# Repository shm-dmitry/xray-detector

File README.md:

V3 version in progress.
V2 version details:

xray-detector, based on SBT-11A sensor, combined with powerbank futures.

At this moment project finished. Everething works, but with several UI-bugs :)

I will fix them in future, but basically project finished.

Features:
- xray-detector on SBT-11A sensor (senses beta & gamma radiation)
- history in sievert, monthly dose, graph with last severall minutes
- beta-radiation rameasurement feature
- flashlight :-)
- powerbank
- long battery life (about half-year) without recharging
- Simple upgrade firmware - Flushing USB port can be accessed with-out unboxing

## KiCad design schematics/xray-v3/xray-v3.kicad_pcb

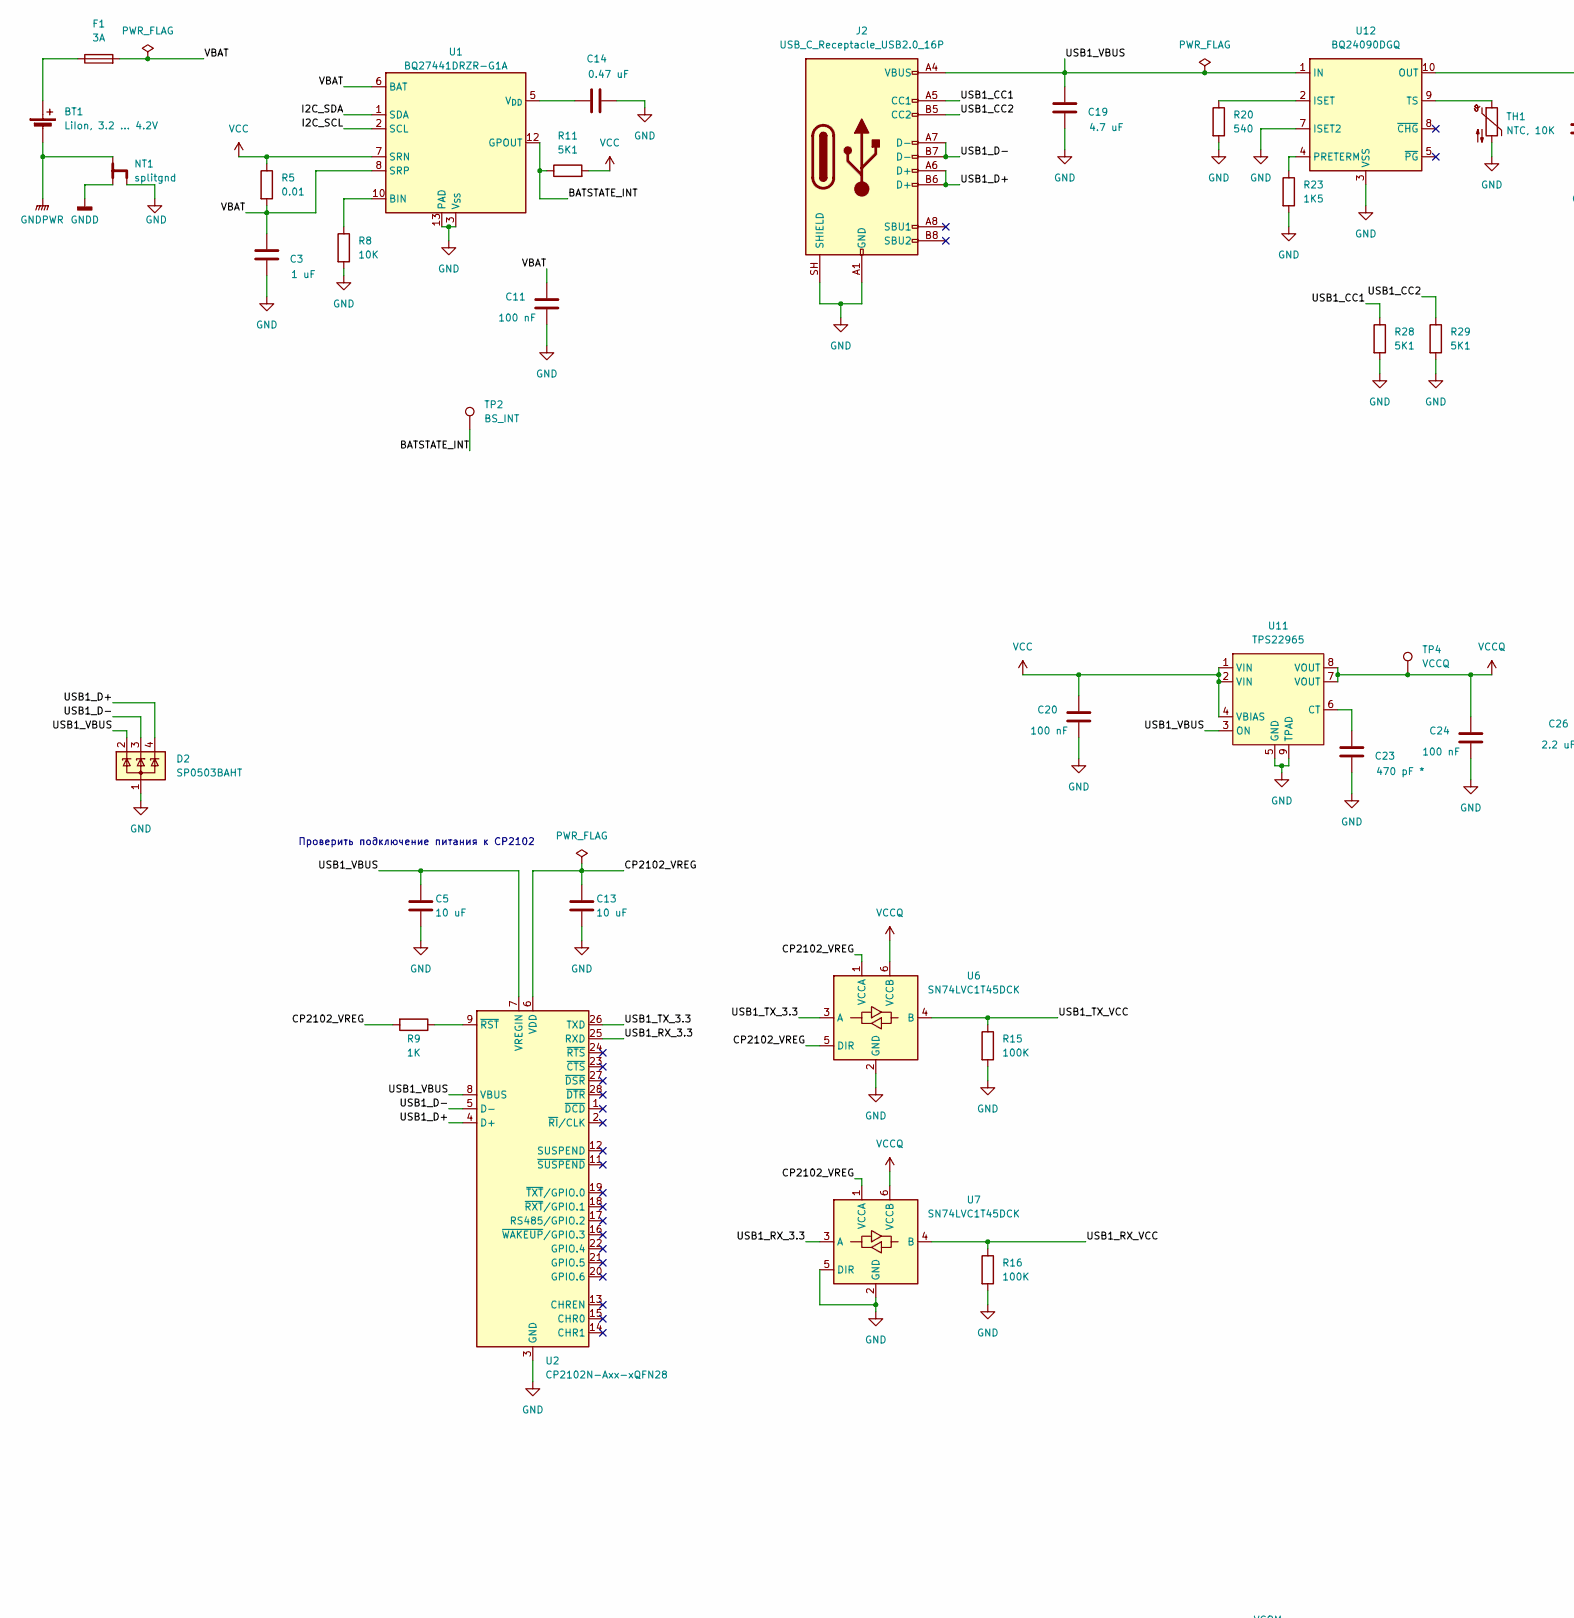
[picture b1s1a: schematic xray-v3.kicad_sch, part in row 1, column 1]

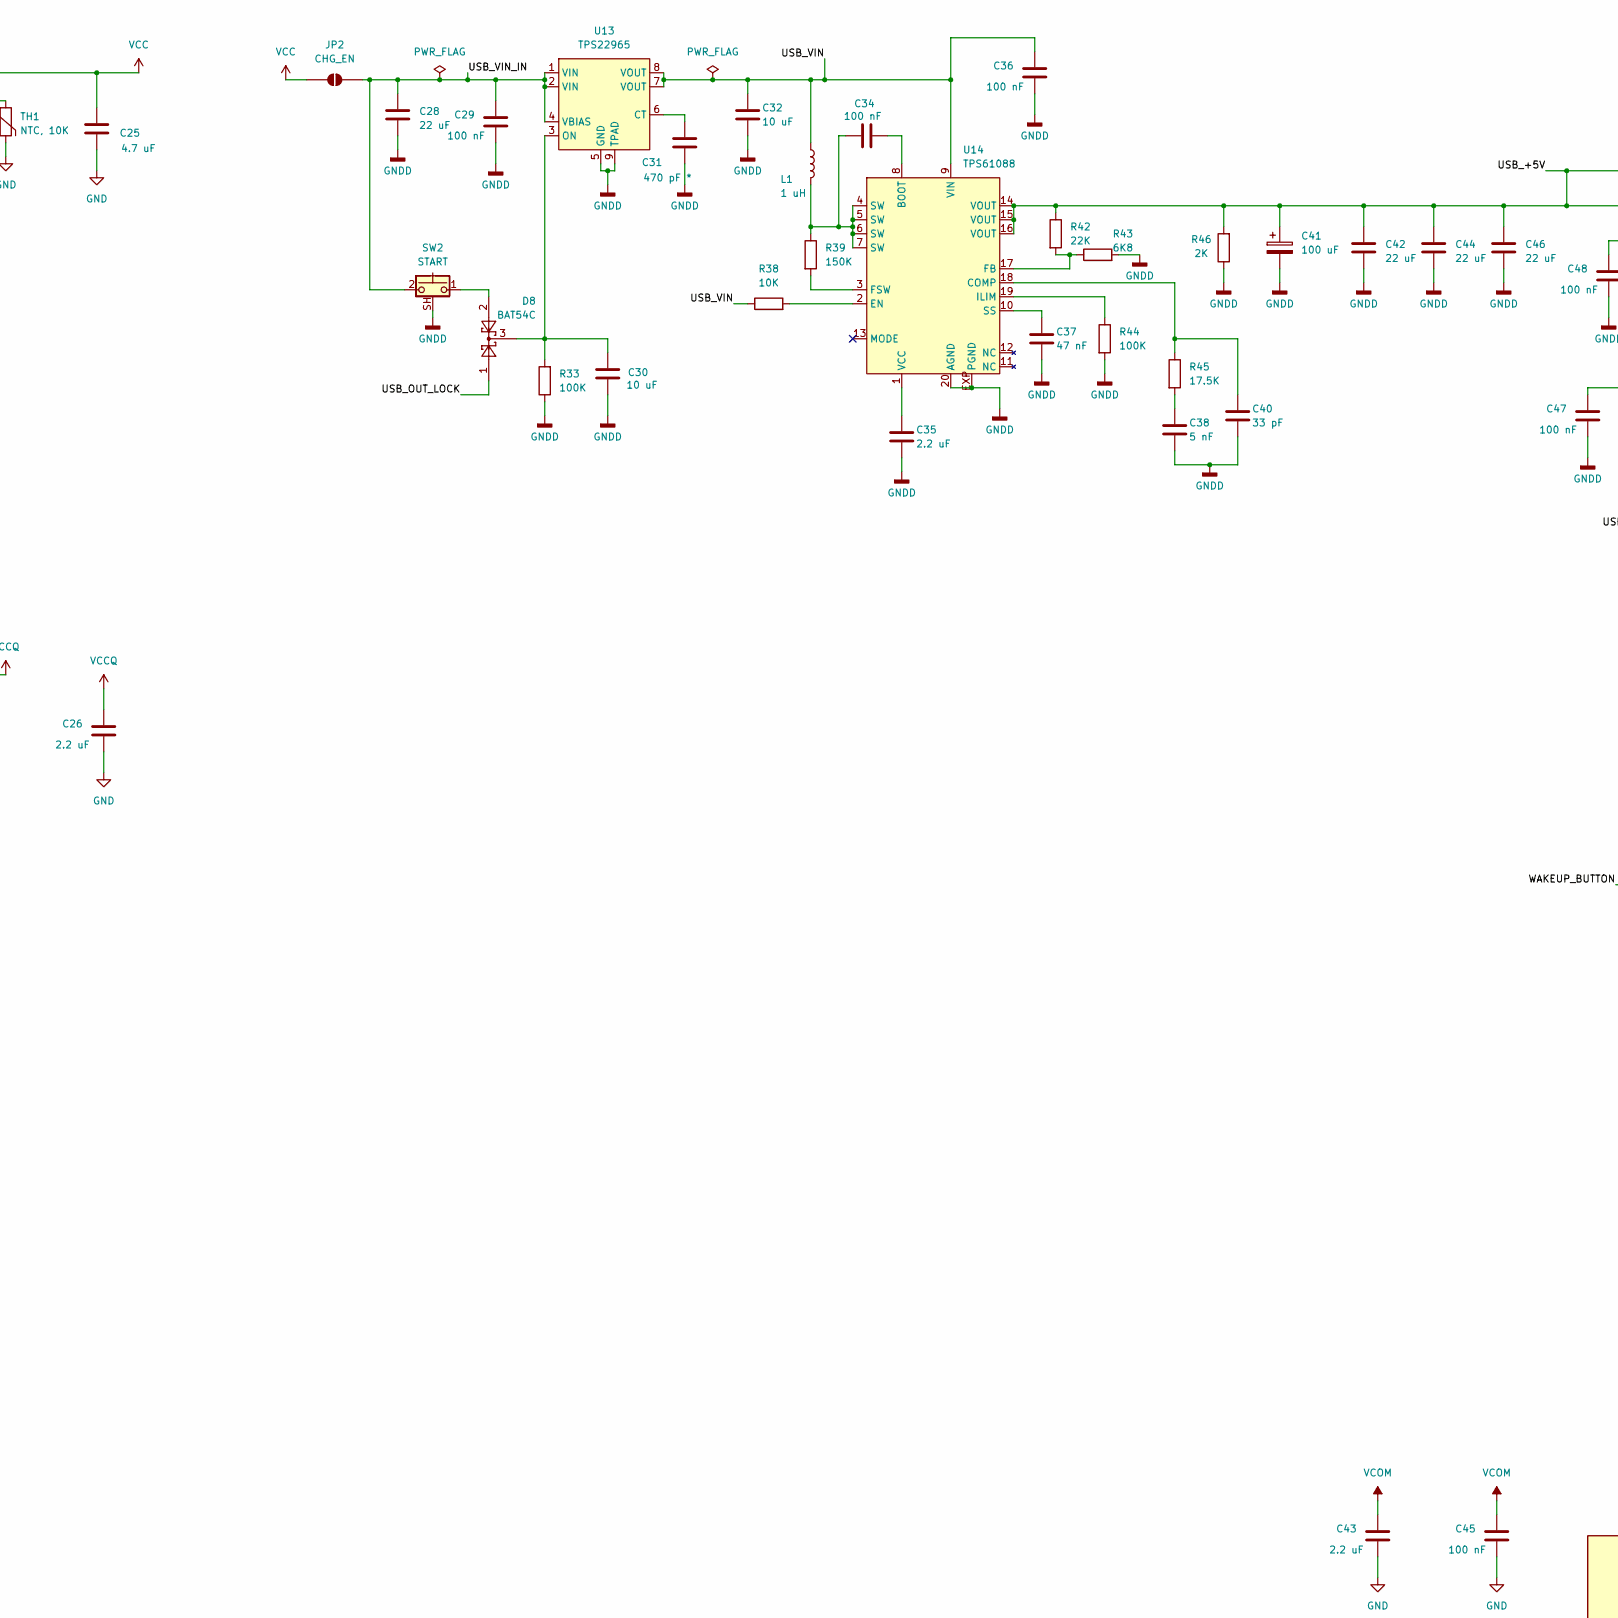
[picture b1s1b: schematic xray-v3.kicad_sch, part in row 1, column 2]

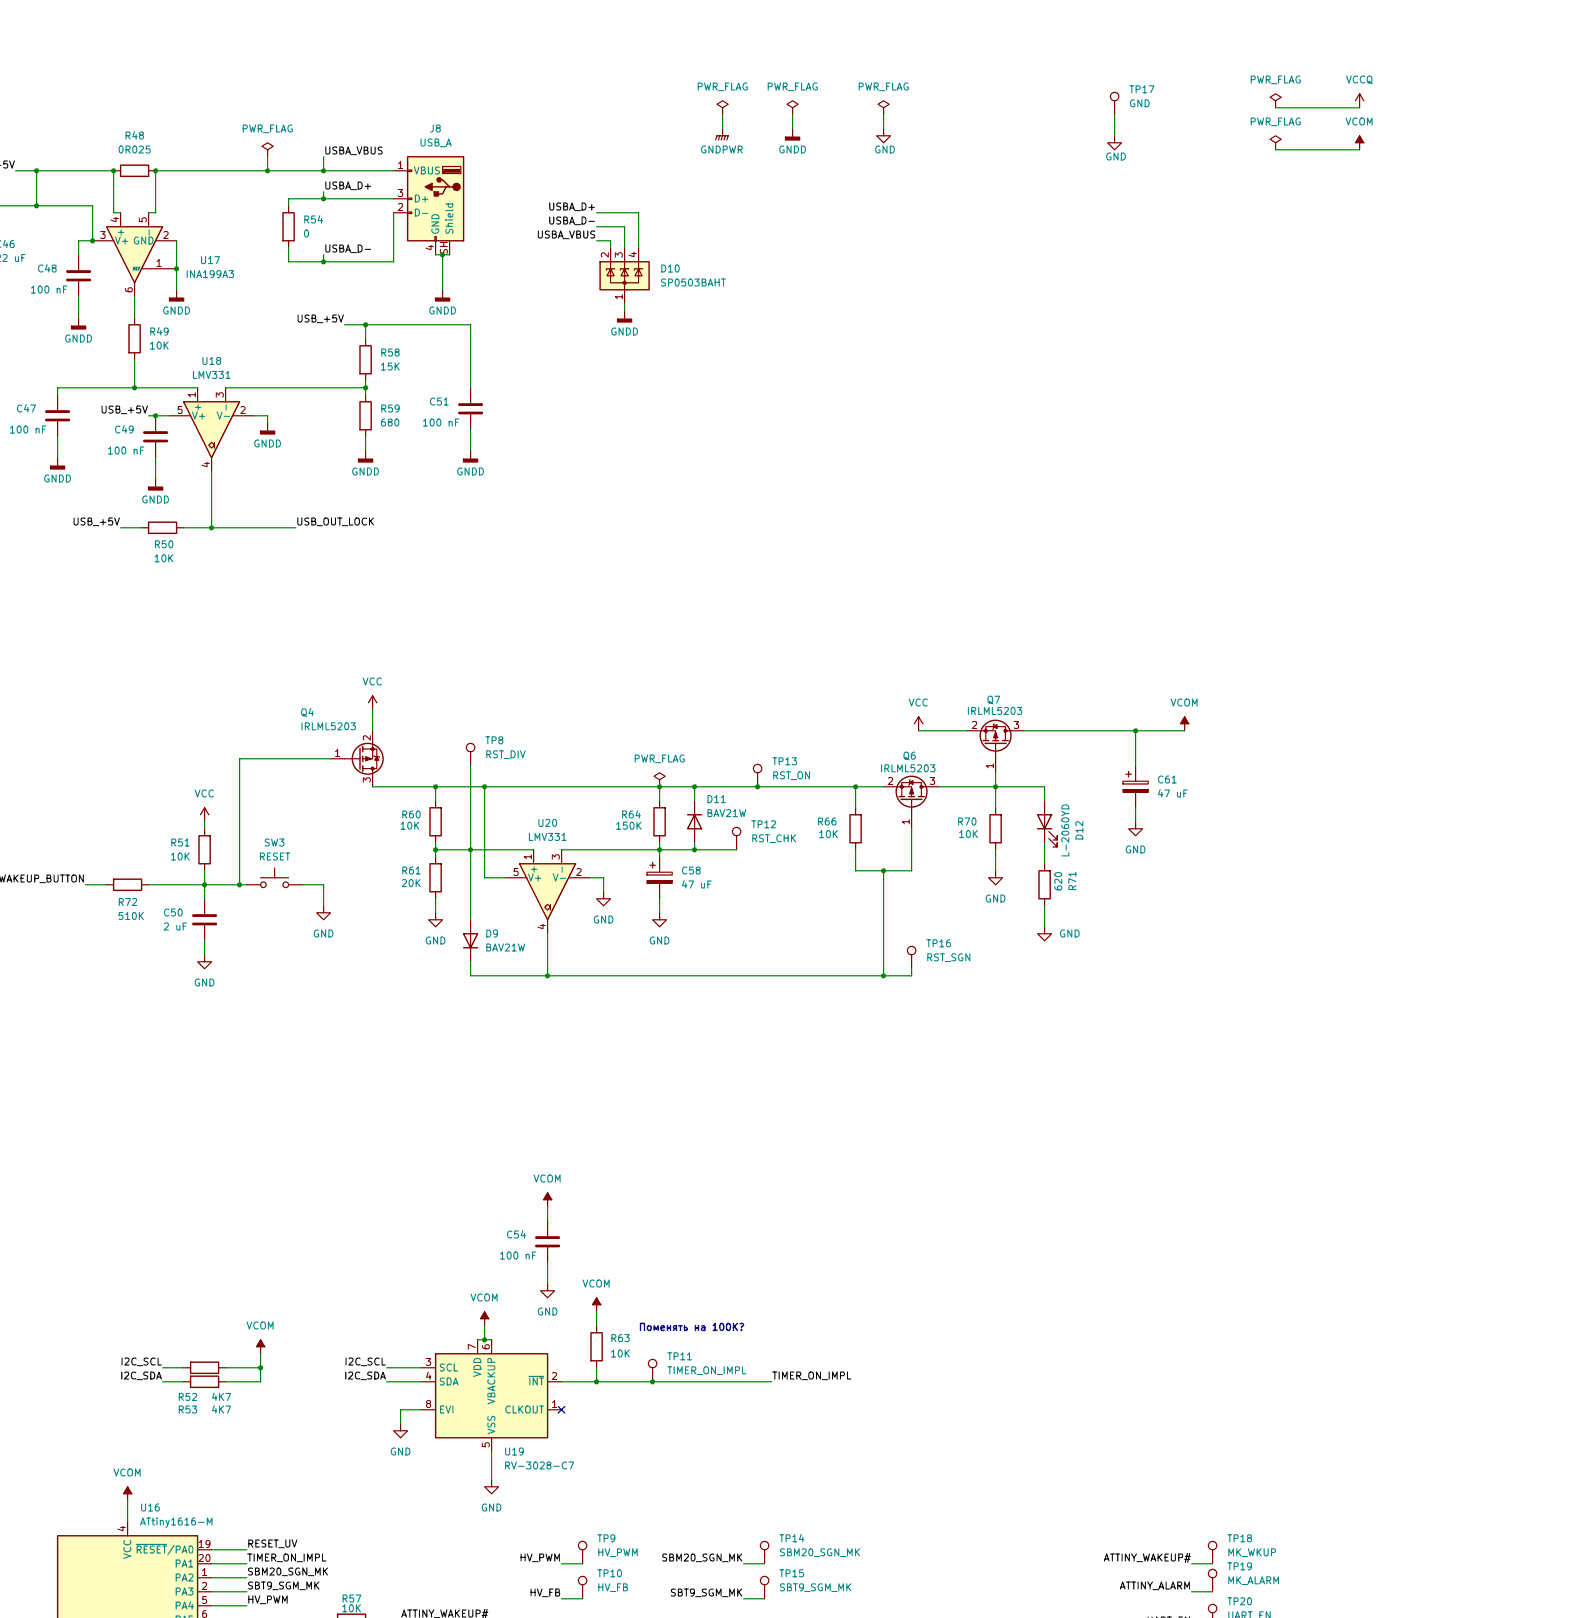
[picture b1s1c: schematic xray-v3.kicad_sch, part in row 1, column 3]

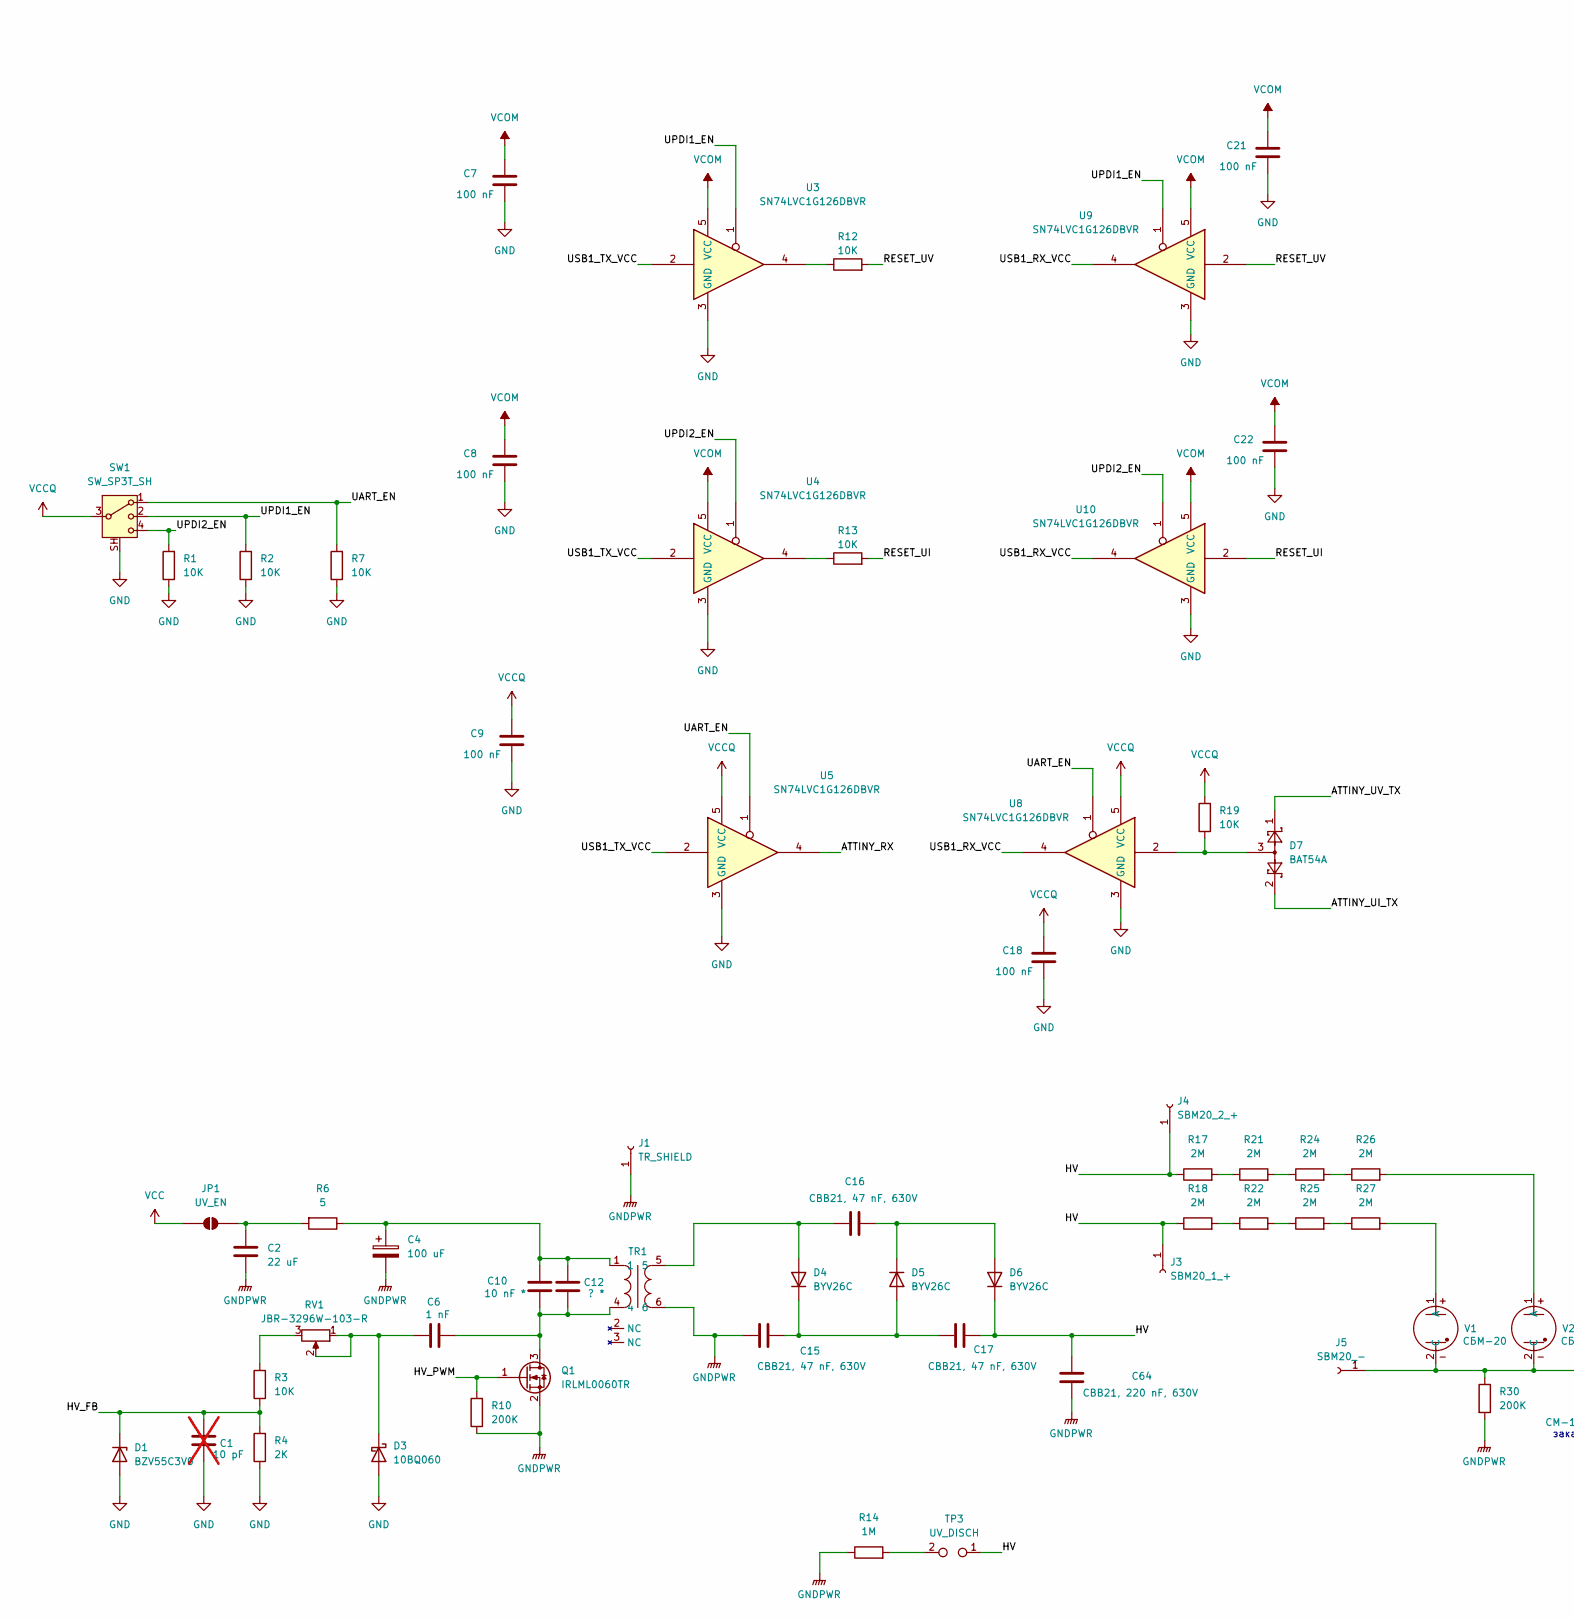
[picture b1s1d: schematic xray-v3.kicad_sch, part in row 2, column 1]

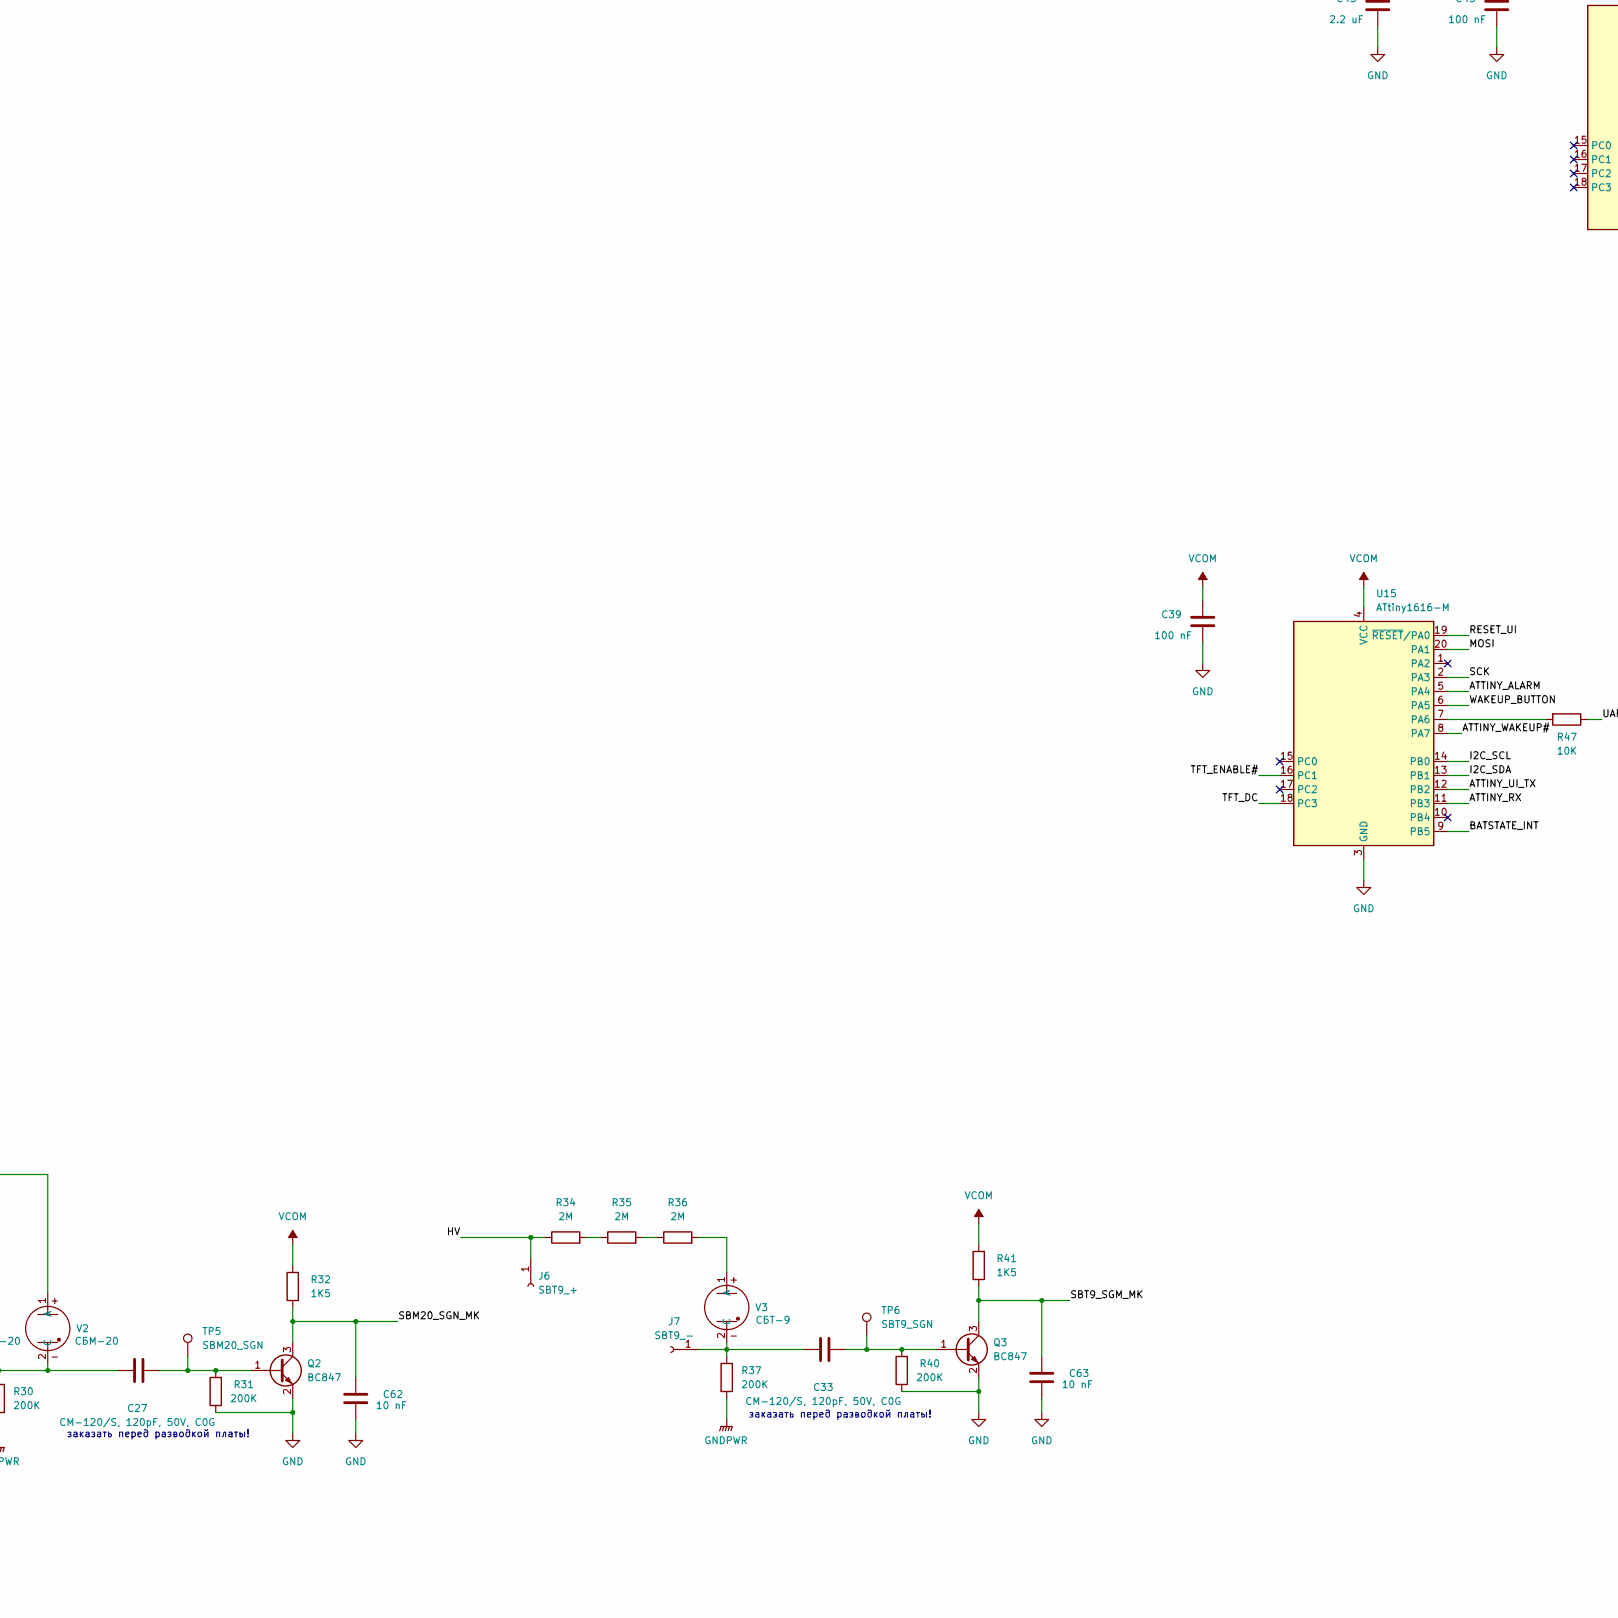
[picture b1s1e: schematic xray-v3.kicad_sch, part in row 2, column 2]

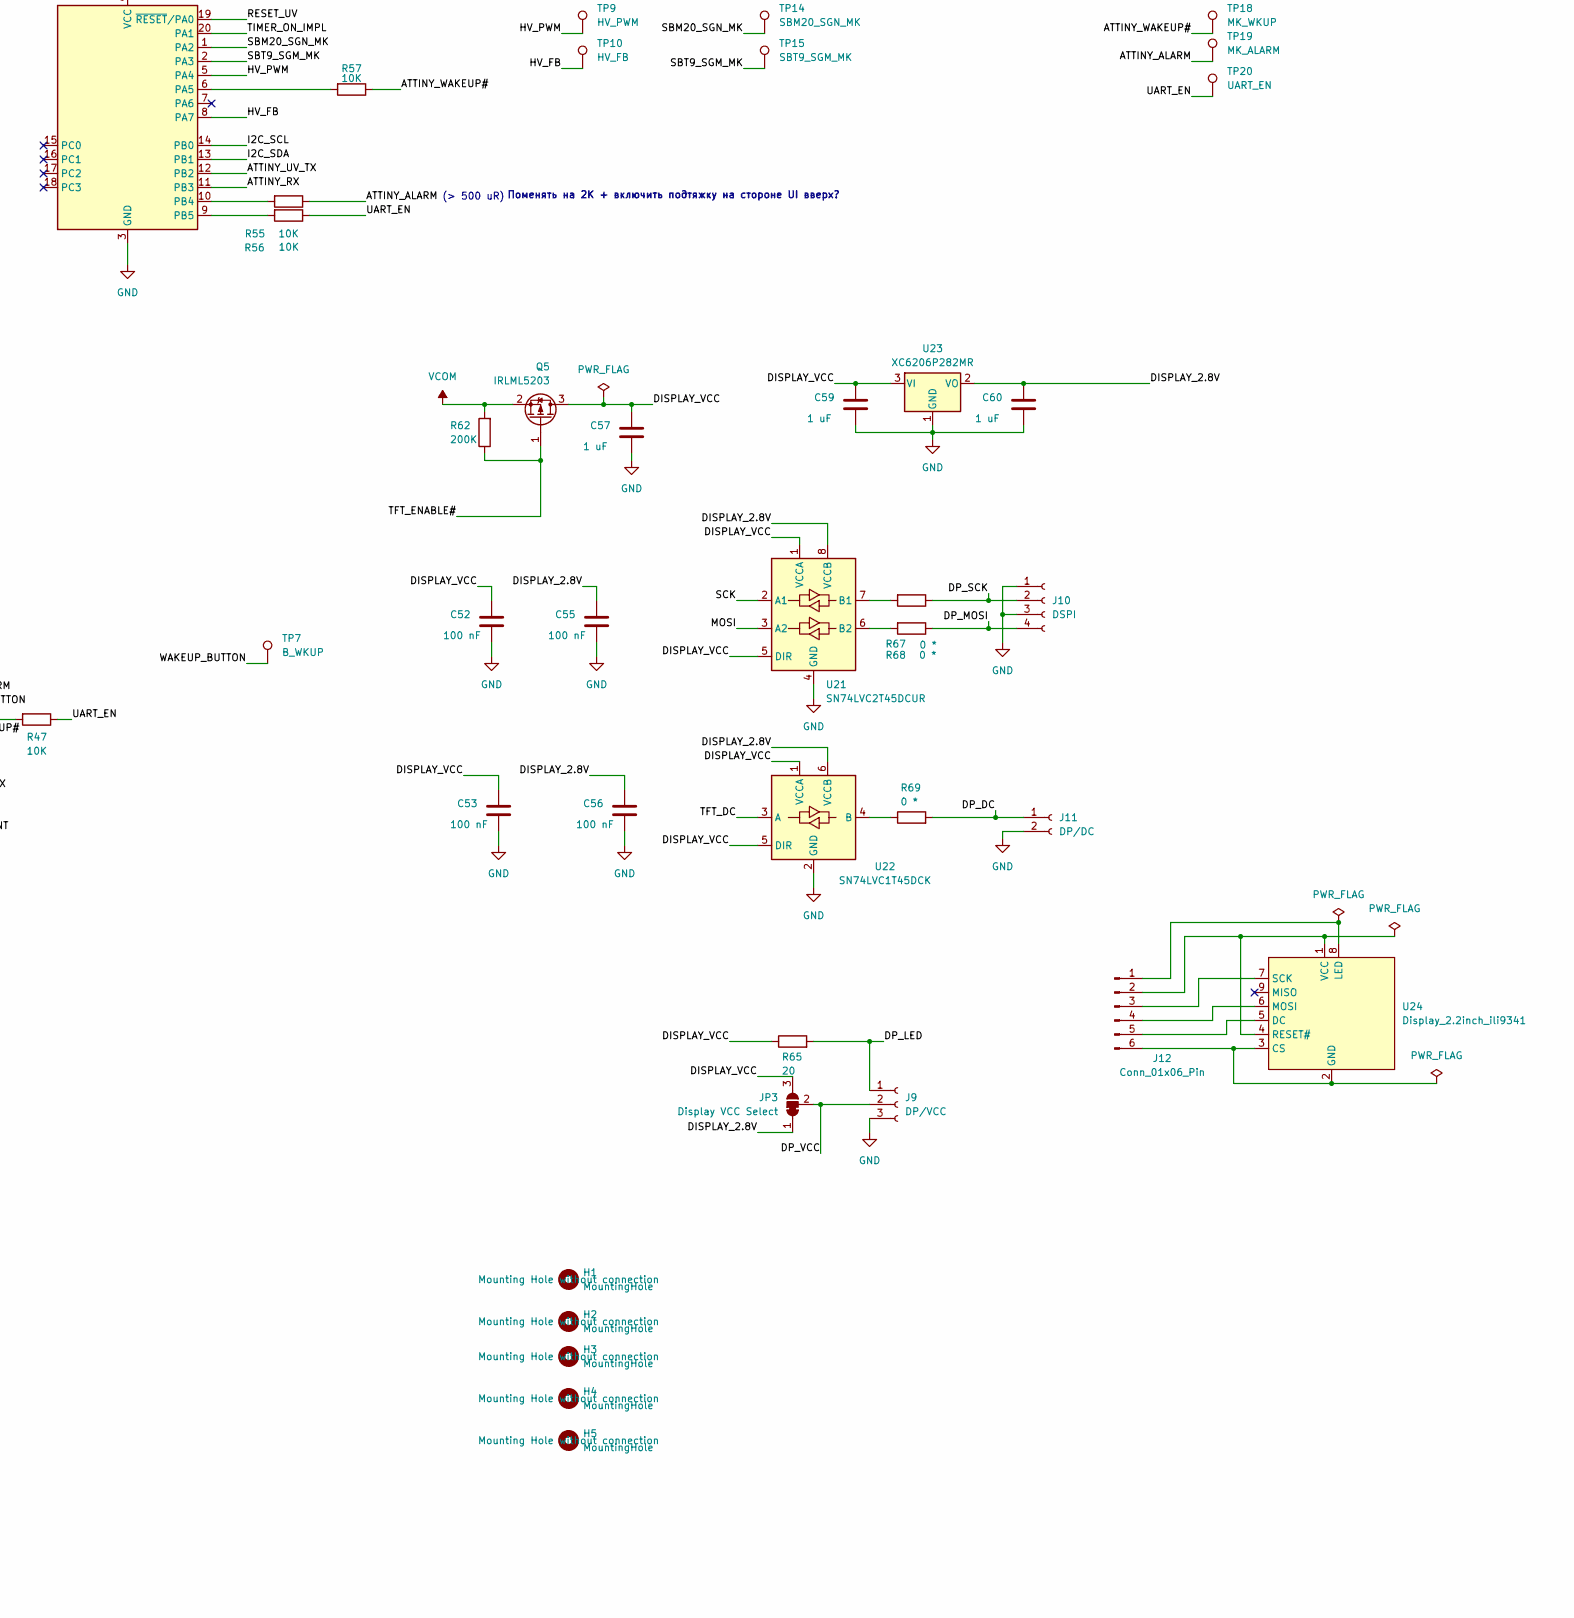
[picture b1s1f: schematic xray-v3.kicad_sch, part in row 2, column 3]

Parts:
BT1: LiIon, 3.2 ... 4.2V; SolderWire-0.75sqmm_1x02_P7mm_D1.25mm_OD3.5mm
C1: 10 pF; C_0603_1608Metric; not fitted
C2, C28, C42, C44, C46: 22 uF; C_1210_3225Metric
C3, C57, C59, C60: 1 uF; C_0603_1608Metric
C4, C41: 100 uF; CP_EIA-6032-28_Kemet-C_HandSolder
C5, C13, C30, C32: 10 uF; C_0603_1608Metric
C6: 1 nF; C_0603_1608Metric
C7, C8, C9, C11, C18, C20, C21, C22, C24, C29, C34, C36, C39, C45, C47, C48, C49, C51, C52, C53, C54, C55, C56: 100 nF; C_0603_1608Metric
C10: 10 nF *; C_0603_1608Metric
C12: ? *; C_0603_1608Metric
C14: 0.47 uF; C_0603_1608Metric
C15, C16, C17: CBB21, 47 nF, 630V; C_Rect_L13.0mm_W6.5mm_P7.50mm_P10.00mm
C19, C25: 4.7 uF; C_0603_1608Metric
C23, C31: 470 pF *; C_0603_1608Metric
C26, C35, C43: 2.2 uF; C_0603_1608Metric
C27, C33: CM-120/S, 120pF, 50V, C0G; C_Disc_D5.0mm_W2.5mm_P2.50mm
C37: 47 nF; C_0603_1608Metric
C38: 5 nF; C_0603_1608Metric
C40: 33 pF; C_0603_1608Metric
C50: 2 uF; C_0603_1608Metric
C58, C61: 47 uF; CP_EIA-3528-21_Kemet-B_HandSolder
C62, C63: 10 nF; C_0603_1608Metric
C64: CBB21, 220 nF, 630V; C_Rect_L13.0mm_W6.5mm_P7.50mm_P10.00mm
D1: BZV55C3V0; D_MiniMELF
D2, D10: SP0503BAHT; SOT-143
D3: 10BQ060; D_SMB_Handsoldering
D4, D5, D6: BYV26C; D_5W_P10.16mm_Horizontal
D7: BAT54A; SOT-23
D8: BAT54C; SOT-23
D9, D11: BAV21W; D_SOD-123
D12: L-2060YD; LED_D1.8mm_W3.3mm_H2.4mm
F1: 3A; FuseHolder1808
H1, H2, H3, H4, H5: MountingHole; MountingHole_2.2mm_M2
J1: TR_SHIELD; SolderWirePad_1x01_SMD_2x4mm
J2: USB_C_Receptacle_USB2.0_16P; USB_C_P16_MIDMOUNT_1.6
J3: SBM20_1_+; SolderWirePad_1x01_SMD_2x4mm
J4: SBM20_2_+; SolderWirePad_1x01_SMD_2x4mm
J5: SBM20_-; SolderWirePad_1x01_SMD_2x4mm
J6: SBT9_+; SolderWirePad_1x01_SMD_2x4mm
J7: SBT9_-; SolderWirePad_1x01_SMD_2x4mm
J8: USB_A
J9: DP/VCC; JST_XH_B3B-XH-A_1x03_P2.50mm_Vertical
J10: DSPI; JST_XH_B4B-XH-A_1x04_P2.50mm_Vertical
J11: DP/DC; JST_XH_B2B-XH-A_1x02_P2.50mm_Vertical
J12: Conn_01x06_Pin
JP1: UV_EN; SolderedJumper-2P-2mm
JP2: CHG_EN; SolderedJumper-2P-2mm
JP3: Display VCC Select; SolderJumper-3_P1.3mm_Bridged12_RoundedPad1.0x1.5mm_NumberL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
L1: 1 uH; L_Bourns_SRP1050WA
NT1: splitgnd; NetTie-3_SMD_Pad2.0mm
Q1: IRLML0060TR; SOT-23
Q2, Q3: BC847; SOT-23
Q4, Q5, Q6, Q7: IRLML5203; SOT-23
R1, R2, R3, R7, R8, R12, R13, R19, R38, R47, R49, R50, R51, R55, R56, R57, R60, R63, R66, R70: 10K; R_0805_2012Metric_Pad1.20x1.40mm_HandSolder
R4, R46: 2K; R_0805_2012Metric_Pad1.20x1.40mm_HandSolder
R5: 0.01; R_2512_6332Metric
R6: 5; R_0805_2012Metric_Pad1.20x1.40mm_HandSolder
R9: 1K; R_0805_2012Metric_Pad1.20x1.40mm_HandSolder
R10, R30, R31, R37, R40, R62: 200K; R_0805_2012Metric_Pad1.20x1.40mm_HandSolder
R11, R28, R29: 5K1; R_0805_2012Metric_Pad1.20x1.40mm_HandSolder
R14: 1M; R_0805_2012Metric_Pad1.20x1.40mm_HandSolder
R15, R16, R33, R44: 100K; R_0805_2012Metric_Pad1.20x1.40mm_HandSolder
R17, R18, R21, R22, R24, R25, R26, R27, R34, R35, R36: 2M; R_0805_2012Metric_Pad1.20x1.40mm_HandSolder
R20: 540; R_0805_2012Metric_Pad1.20x1.40mm_HandSolder
R23, R32, R41: 1K5; R_0805_2012Metric_Pad1.20x1.40mm_HandSolder
R39, R64: 150K; R_0805_2012Metric_Pad1.20x1.40mm_HandSolder
R42: 22K; R_0805_2012Metric_Pad1.20x1.40mm_HandSolder
R43: 6K8; R_0805_2012Metric_Pad1.20x1.40mm_HandSolder
R45: 17.5K; R_0805_2012Metric_Pad1.20x1.40mm_HandSolder
R48: 0R025; R_2512_6332Metric
R52, R53: 4K7; R_0805_2012Metric_Pad1.20x1.40mm_HandSolder
R54: 0; R_0805_2012Metric_Pad1.20x1.40mm_HandSolder
R58: 15K; R_0805_2012Metric_Pad1.20x1.40mm_HandSolder
R59: 680; R_0805_2012Metric_Pad1.20x1.40mm_HandSolder
R61: 20K; R_0805_2012Metric_Pad1.20x1.40mm_HandSolder
R65: 20; R_0805_2012Metric_Pad1.20x1.40mm_HandSolder
R67, R68, R69: 0 *; R_0805_2012Metric_Pad1.20x1.40mm_HandSolder
R71: 620; R_0805_2012Metric_Pad1.20x1.40mm_HandSolder
R72: 510K; R_0805_2012Metric_Pad1.20x1.40mm_HandSolder
RV1: JBR-3296W-103-R; Potentiometer_Bourns_3296W_Vertical
SW1: SW_SP3T_SH; SK13D07VG4
SW2: START; SW_Tactile_SKHH_Angled_SH
SW3: RESET; SW_TH_Tactile_Omron_B3F-107x
TH1: NTC, 10K; SolderWire-0.25sqmm_1x02_P4.2mm_D0.65mm_OD1.7mm
TP2: BS_INT; TestPoint_Loop_D2.50mm_Drill1.0mm
TP3: UV_DISCH; TestPoint_2Pads_Pitch5.08mm_Drill1.3mm
TP4: VCCQ; TestPoint_Pad_1.0x1.0mm
TP5: SBM20_SGN; TestPoint_Pad_1.0x1.0mm
TP6: SBT9_SGN; TestPoint_Pad_1.0x1.0mm
TP7: B_WKUP; TestPoint_Pad_1.0x1.0mm
TP8: RST_DIV; TestPoint_Pad_1.0x1.0mm
TP9: HV_PWM; TestPoint_Loop_D2.50mm_Drill1.0mm
TP10: HV_FB; TestPoint_Loop_D2.50mm_Drill1.0mm
TP11: TIMER_ON_IMPL; TestPoint_Pad_1.0x1.0mm
TP12: RST_CHK; TestPoint_Pad_1.0x1.0mm
TP13: RST_ON; TestPoint_Pad_1.0x1.0mm
TP14: SBM20_SGN_MK; TestPoint_Loop_D2.50mm_Drill1.0mm
TP15: SBT9_SGM_MK; TestPoint_Loop_D2.50mm_Drill1.0mm
TP16: RST_SGN; TestPoint_Pad_1.0x1.0mm
TP17: GND; TestPoint_THTPad_3.0x3.0mm_Drill1.5mm
TP18: MK_WKUP; TestPoint_Pad_1.0x1.0mm
TP19: MK_ALARM; TestPoint_Pad_1.0x1.0mm
TP20: UART_EN; TestPoint_Pad_1.0x1.0mm
TR1: transformator_SMD_MICRO_EE0504S
U1: BQ27441DRZR-G1A; Texas_S-PDSO-N12_novia
U2: CP2102N-Axx-xQFN28; QFN-28-1EP_5x5mm_P0.5mm_EP3.35x3.35mm
U3, U4, U5, U8, U9, U10: SN74LVC1G126DBVR; SOT-23-5
U6, U7, U22: SN74LVC1T45DCK; SOT-363_SC-70-6
U11, U13: TPS22965; WSON-8-1EP_3x2.5mm_P0.5mm_EP1.2x1.5mm_PullBack
U12: BQ24090DGQ; MSOP-10-1EP_3x3mm_P0.5mm_EP1.73x1.98mm
U14: TPS61088; VQFN_20
U15, U16: ATtiny1616-M; VQFN-20-1EP_3x3mm_P0.4mm_EP1.7x1.7mm
U17: INA199A3; SOT-363_SC-70-6
U18, U20: LMV331; SOT-23-5_HandSoldering
U19: RV-3028-C7; MicroCrystal_C7_SON-8_1.5x3.2mm_P0.9mm
U21: SN74LVC2T45DCUR; VSSOP-8_2.3x2mm_P0.5mm
U23: XC6206P282MR; SOT-23-3
U24: Display_2.2inch_ili9341; JST_XH_B9B-XH-A_1x09_P2.50mm_Vertical
V1, V2: СБМ-20; SolderWire-0.5sqmm_1x02_P4.8mm_D0.9mm_OD2.3mm
V3: СБТ-9; SolderWire-0.5sqmm_1x02_P4.8mm_D0.9mm_OD2.3mm

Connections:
/ATTINY_ALARM: R55.1, TP19.1 (1_1), U15.5 (PA4)
/ATTINY_RX: U5.4, U15.11 (PB3), U16.11 (PB3)
/ATTINY_UI_TX: D7.2, U15.12 (PB2)
/ATTINY_UV_TX: D7.1, U16.12 (PB2)
/ATTINY_WAKEUP#: R57.1, TP18.1 (1_1), U15.8 (PA7)
/BATSTATE_INT: R11.1, TP2.1 (1_1), U1.12 (GPOUT), U15.9 (PB5)
/CP2102_VREG: C13.1, R9.2, U2.6 (VDD), U6.1 (VCCA), U6.5 (DIR), U7.1 (VCCA)
/DISPLAY_2.8V: C55.1, C56.1, C60.1, JP3.1 (A), U21.8 (VCCB), U22.6 (VCCB), U23.2 (VO)
/DISPLAY_VCC: C52.1, C53.1, C57.1, C59.1, JP3.3 (B), Q5.3 (D), R65.1, U21.1 (VCCA), U21.5 (DIR), U22.1 (VCCA), U22.5 (DIR), U23.3 (VI)
/DP_DC: J11.1, R69.2
/DP_LED: J9.1, R65.2
/DP_MOSI: J10.4, R68.1
/DP_SCK: J10.2, R67.1
/DP_VCC: J9.2, JP3.2 (C)
/HV: C17.2, C64.2, D6.1 (K), J3.1 (Pin_1_1), J4.1 (Pin_1_1), J6.1 (Pin_1_1), R17.1, R18.1, R34.1, TP3.1
/HV_FB: C1.1, D1.1 (K), R3.1, R4.2, TP10.1 (1_1), U16.8 (PA7)
/HV_PWM: Q1.1 (G), R10.2, TP9.1 (1_1), U16.5 (PA4)
/I2C_SCL: R52.2, U1.2 (SCL), U15.14 (PB0), U16.14 (PB0), U19.3 (SCL)
/I2C_SDA: R53.2, U1.1 (SDA), U15.13 (PB1), U16.13 (PB1), U19.4 (SDA)
/MOSI: U15.20 (PA1), U21.3 (A2)
/RESET_UI: R13.2, U10.2, U15.19 (~RESET/PA0)
/RESET_UV: R12.2, U9.2, U16.19 (~RESET/PA0)
/SBM20_SGN_MK: C62.1, Q2.3 (C), R32.1, TP14.1 (1_1), U16.1 (PA2)
/SBT9_SGM_MK: C63.1, Q3.3 (C), R41.1, TP15.1 (1_1), U16.2 (PA3)
/SCK: U15.2 (PA3), U21.2 (A1)
/TFT_DC: U15.18 (PC3), U22.3 (A)
/TFT_ENABLE#: Q5.1 (G), R62.1, U15.16 (PC1)
/TIMER_ON_IMPL: R63.2, TP11.1 (1_1), U16.20 (PA1), U19.2 (~INT)
/UART_EN: R7.2, R47.1, R56.1, SW1.1, TP20.1 (1_1), U5.1, U8.1
/UPDI1_EN: R2.2, SW1.2, U3.1, U9.1
/UPDI2_EN: R1.2, SW1.4, U4.1, U10.1
/USB1_CC1: J2.A5 (CC1), R28.1
/USB1_CC2: J2.B5 (CC2), R29.1
/USB1_D+: D2.4 (K), J2.A6 (D+), J2.B6 (D+), U2.4 (D+)
/USB1_D-: D2.3 (K), J2.A7 (D-), J2.B7 (D-), U2.5 (D-)
/USB1_RX_3.3: U2.25 (RXD), U7.3 (A)
/USB1_RX_VCC: R16.1, U7.4 (B), U8.4, U9.4, U10.4
/USB1_TX_3.3: U2.26 (TXD), U6.3 (A)
/USB1_TX_VCC: R15.1, U3.2, U4.2, U5.2, U6.4 (B)
/USB1_VBUS: C5.1, C19.1, D2.2 (K), J2.A4 (VBUS), J2.A9 (VBUS), J2.B4 (VBUS), J2.B9 (VBUS), U2.7 (VREGIN), U2.8 (VBUS), U11.3 (ON), U12.1 (IN)
/USBA_D+: D10.4 (K), J8.3 (D+), R54.1
/USBA_D-: D10.3 (K), J8.2 (D-), R54.2
/USBA_VBUS: D10.2 (K), J8.1 (VBUS), R48.2, U17.5 (-)
/USB_+5V: C41.1, C42.1, C44.1, C46.1, C48.1, C49.1, C51.1, R42.1, R46.2, R48.1, R50.1, R58.1, U14.14 (VOUT), U14.15 (VOUT), U14.16 (VOUT), U17.3 (V+), U17.4 (+), U18.5 (V+)
/USB_OUT_LOCK: D8.1, R50.2, U18.4
/USB_VIN: C32.1, C36.1, L1.1, R38.1, U13.7 (VOUT), U13.8 (VOUT), U14.9 (VIN)
/USB_VIN_IN: C28.1, C29.1, JP2.2 (B), SW2.2, U13.1 (VIN), U13.2 (VIN), U13.4 (VBIAS)
/VBAT: C3.1, C11.1, F1.2, R5.2, U1.6 (BAT), U1.8 (SRP)
/WAKEUP_BUTTON: R72.2, TP7.1 (1_1), U15.6 (PA5)
GND: C1.2, C3.2, C5.2, C7.2, C8.2, C9.2, C11.2, C13.2, C14.2, C18.2, C19.2, C20.2, C21.2, C22.2, C23.2, C24.2, C25.2, C26.2, C39.2, C43.2, C45.2, C50.1, C52.2, C53.2, C54.2, C55.2, C56.2, C57.2, C58.2, C59.2, C60.2, C61.2, C62.2, C63.2, D1.2 (A), D2.1 (A), D3.2 (A), J2.A1 (GND), J2.A12 (GND), J2.B1 (GND), J2.B12 (GND), J2.SH (SHIELD), J9.3, J10.1, J10.3, J11.2, NT1.3, Q2.2 (E), Q3.2 (E), R1.1, R2.1, R4.1, R7.1, R8.2, R15.2, R16.2, R20.2, R23.2, R28.2, R29.2, R31.1, R40.1, R61.1, R70.1, R71.1, SW1.SH, SW3.1, TH1.2, TP17.1 (1_1), U1.3 (V_{SS}), U1.13 (PAD), U2.3 (GND), U2.29 (GND), U3.3 (GND), U4.3 (GND), U5.3 (GND), U6.2 (GND), U7.2 (GND), U7.5 (DIR), U8.3 (GND), U9.3 (GND), U10.3 (GND), U11.5 (GND), U11.9 (TPAD), U12.3 (VSS), U12.7 (ISET2), U12.11 (VSS), U15.3 (GND), U15.21 (GND), U16.3 (GND), U16.21 (GND), U19.5 (VSS), U19.8 (EVI), U20.2 (V-), U21.4 (GND), U22.2 (GND), U23.1 (GND)
GNDD: C28.2, C29.2, C30.2, C31.2, C32.2, C35.2, C36.2, C37.2, C38.2, C40.2, C41.2, C42.2, C44.2, C46.2, C47.2, C48.2, C49.2, C51.2, D10.1 (A), J8.4 (GND), J8.SH (Shield), NT1.1, R33.1, R43.2, R44.2, R46.1, R59.2, SW2.SH (B), U13.5 (GND), U13.9 (TPAD), U14.20 (AGND), U14.EXP (PGND), U17.1 (REF), U17.2 (GND), U18.2 (V-)
GNDPWR: BT1.2 (-), C2.2, C4.2, C15.1, C64.1, J1.1 (Pin_1_1), NT1.2, Q1.2 (S), R10.1, R14.1, R30.2, R37.2, TR1.6
unnamed: BT1.1 (+), F1.1
unnamed: C4.1, C10.2, C12.2, R6.1, TR1.1
unnamed: C34.2, L1.2, R39.1, U14.4 (SW), U14.5 (SW), U14.6 (SW), U14.7 (SW)
unnamed: C38.1, R45.2
unnamed: C6.2, D3.1 (K), RV1.1, RV1.2
unnamed: C16.1, D4.2 (A), TR1.5
unnamed: C15.2, C17.1, D4.1 (K), D5.2 (A)
unnamed: C16.2, D5.1 (K), D6.2 (A)
unnamed: D7.3, R19.1, U8.2
unnamed: D8.2, SW2.1
unnamed: D9.2 (A), R60.1, R61.2, TP8.1 (1_1), U20.1 (+)
unnamed: D9.1 (K), Q6.1 (G), R66.1, TP16.1 (1_1), U20.4
unnamed: C58.1, D11.2 (A), R64.1, TP12.1 (1_1), U20.3 (-)
unnamed: D11.1 (K), Q4.3 (D), Q6.2 (S), R60.2, R64.2, R66.2, TP13.1 (1_1), U20.5 (V+)
unnamed: D12.2 (A), Q6.3 (D), Q7.1 (G), R70.2
unnamed: D12.1 (K), R71.2
unnamed: C27.1, J5.1 (Pin_1_1), R30.1, V1.2 (C), V2.2 (C)
unnamed: C33.1, J7.1 (Pin_1_1), R37.1, V3.2 (C)
unnamed: J12.1, U24.8 (LED)
unnamed: J12.2, U24.1 (VCC), U24.4 (RESET#)
unnamed: J12.3, U24.7 (SCK)
unnamed: J12.4, U24.6 (MOSI)
unnamed: J12.5, U24.5 (DC)
unnamed: J12.6, U24.2 (GND), U24.3 (CS)
unnamed: C2.1, JP1.2 (B), R6.2
unnamed: C6.1, C10.1, C12.1, Q1.3 (D), TR1.4
unnamed: C27.2, Q2.1 (B), R31.2, TP5.1 (1_1)
unnamed: C33.2, Q3.1 (B), R40.2, TP6.1 (1_1)
unnamed: C50.2, Q4.1 (G), R51.1, R72.1, SW3.2
unnamed: R3.2, RV1.3
unnamed: R12.1, U3.4
unnamed: R13.1, U4.4
unnamed: R14.2, TP3.2
unnamed: R17.2, R21.1
unnamed: R18.2, R22.1
unnamed: R21.2, R24.1
unnamed: R22.2, R25.1
unnamed: R24.2, R26.1
unnamed: R25.2, R27.1
unnamed: R26.2, V2.1 (A)
unnamed: R27.2, V1.1 (A)
unnamed: R34.2, R35.1
unnamed: R35.2, R36.1
unnamed: R36.2, V3.1 (A)
unnamed: R49.1, U17.6
unnamed: R8.1, U1.10 (BIN)
unnamed: C14.1, U1.5 (V_{DD})
unnamed: R9.1, U2.9 (~RST)
unnamed: C23.1, U11.6 (CT)
unnamed: R20.1, U12.2 (ISET)
unnamed: R23.1, U12.4 (PRETERM)
unnamed: TH1.1, U12.9 (TS)
unnamed: C31.1, U13.6 (CT)
unnamed: C30.1, D8.3, R33.2, U13.3 (ON)
unnamed: C34.1, U14.8 (BOOT)
unnamed: C40.1, R45.1, U14.18 (COMP)
unnamed: R38.2, U14.2 (EN)
unnamed: R42.2, R43.1, U14.17 (FB)
unnamed: R39.2, U14.3 (FSW)
unnamed: R44.1, U14.19 (ILIM)
unnamed: C37.1, U14.10 (SS)
unnamed: C35.1, U14.1 (VCC)
unnamed: R47.2, U15.7 (PA6)
unnamed: R57.2, U16.6 (PA5)
unnamed: R55.2, U16.10 (PB4)
unnamed: R56.2, U16.9 (PB5)
unnamed: C47.1, R49.2, U18.1 (+)
unnamed: R58.2, R59.1, U18.3 (-)
unnamed: R67.2, U21.7 (B1)
unnamed: R68.2, U21.6 (B2)
unnamed: R69.1, U22.4 (B)
VCC: C20.1, C25.1, JP1.1 (A), JP2.1 (A), Q4.2 (S), Q7.2 (S), R5.1, R11.2, R51.2, U1.7 (SRN), U11.1 (VIN), U11.2 (VIN), U11.4 (VBIAS), U12.10 (OUT)
VCCQ: C9.1, C18.1, C24.1, C26.1, R19.2, SW1.3, TP4.1 (1_1), U5.5 (VCC), U6.6 (VCCB), U7.6 (VCCB), U8.5 (VCC), U11.7 (VOUT), U11.8 (VOUT)
VCOM: C7.1, C8.1, C21.1, C22.1, C39.1, C43.1, C45.1, C54.1, C61.1, Q5.2 (S), Q7.3 (D), R32.2, R41.2, R52.1, R53.1, R62.2, R63.1, U3.5 (VCC), U4.5 (VCC), U9.5 (VCC), U10.5 (VCC), U15.4 (VCC), U16.4 (VCC), U19.6 (VBACKUP), U19.7 (VDD)

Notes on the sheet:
(> 500 uR)
Поменять на 2К + включить подтяжку на стороне UI вверх?
заказать перед разводкой платы!
Проверить подключение питания к CP2102
Поменять на 100К?
